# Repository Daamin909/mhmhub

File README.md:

# mhmhub

Made by [Daamin](https://daamin.tech)

Features:

- USB-C input port
- 3x USB-C ports
- 1x USB-A port
- White Case
- Mounted PCB for stability

## Info

this hub is a 3x usbc port + 1x usba hub. it has a usb-c as the power source and connector to the host. it is also very teeny tiny.

I made this hub since i own a macbook and the hub i owned is pretty cheap and ugly. I wanted this hub to match my white keyboard and macropad. i added usb-a for my harddrives and usb-c for my keyboard and macropad.

## PCB

The PCB's size is 25.5mm x 48.5mm

| Schematic                 |
| ------------------------- |
|  |

| Front                 |
| --------------------- |
|  |

| Back                 |
| -------------------- |
|  |

| 3D - Front               |
| ------------------------ |
|  |

| 3D - Back               |
| ----------------------- |
|  |

## Case

The case was made in Fusion360.

## 3D Render:

## BOM - Products

| Name                 | Qty | Final Price - INR (USD) | Link                                                                                                                                       |
| -------------------- | --- | ----------------------- | ------------------------------------------------------------------------------------------------------------------------------------------ |
| PCBA                 | 2   | 2,597.77 ($30.4)        | [here](https://hc-cdn.hel1.your-objectstorage.com/s/v3/5fce6532436acc2e02ca682e6a3f78e5be402c24_screenshot_2025-06-27_at_7.26.42___pm.png) |
| PCB                  | 5   | 1210.01 ($14.16)        | [here](https://hc-cdn.hel1.your-objectstorage.com/s/v3/5fce6532436acc2e02ca682e6a3f78e5be402c24_screenshot_2025-06-27_at_7.26.42___pm.png) |
| USB-C to USB-C cable | 1   | 350 ($4.1)              | [here](https://amzn.in/d/gBN8jyo)                                                                                                          |
| M2 x 6mm Screws      | 25  | 224 ($2.62)             | [here](https://amzn.in/d/dhuYR6N)                                                                                                          |
| M2 Nuts | 50  | 250 ($2.93)             | [here](https://amzn.in/d/iHDKn9j)                                                                                                          |
| Top Case             | 1   | NA                      | print legion                                                                                                                               |
| Bottom Case          | 1   | NA                      | print legion                                                                                                                               |

## Total Pricing

The total comes out to be approximately 4632 INR ($54.21). Does not include 3D - Printed case.

## Notes :-

I want all the three 3D-printed parts to be printed in white color.

Some of the above items, were ordered in packs due to unavailability of singular items.
The pricing might slightly vary due to flash sales, and dollar market trends.

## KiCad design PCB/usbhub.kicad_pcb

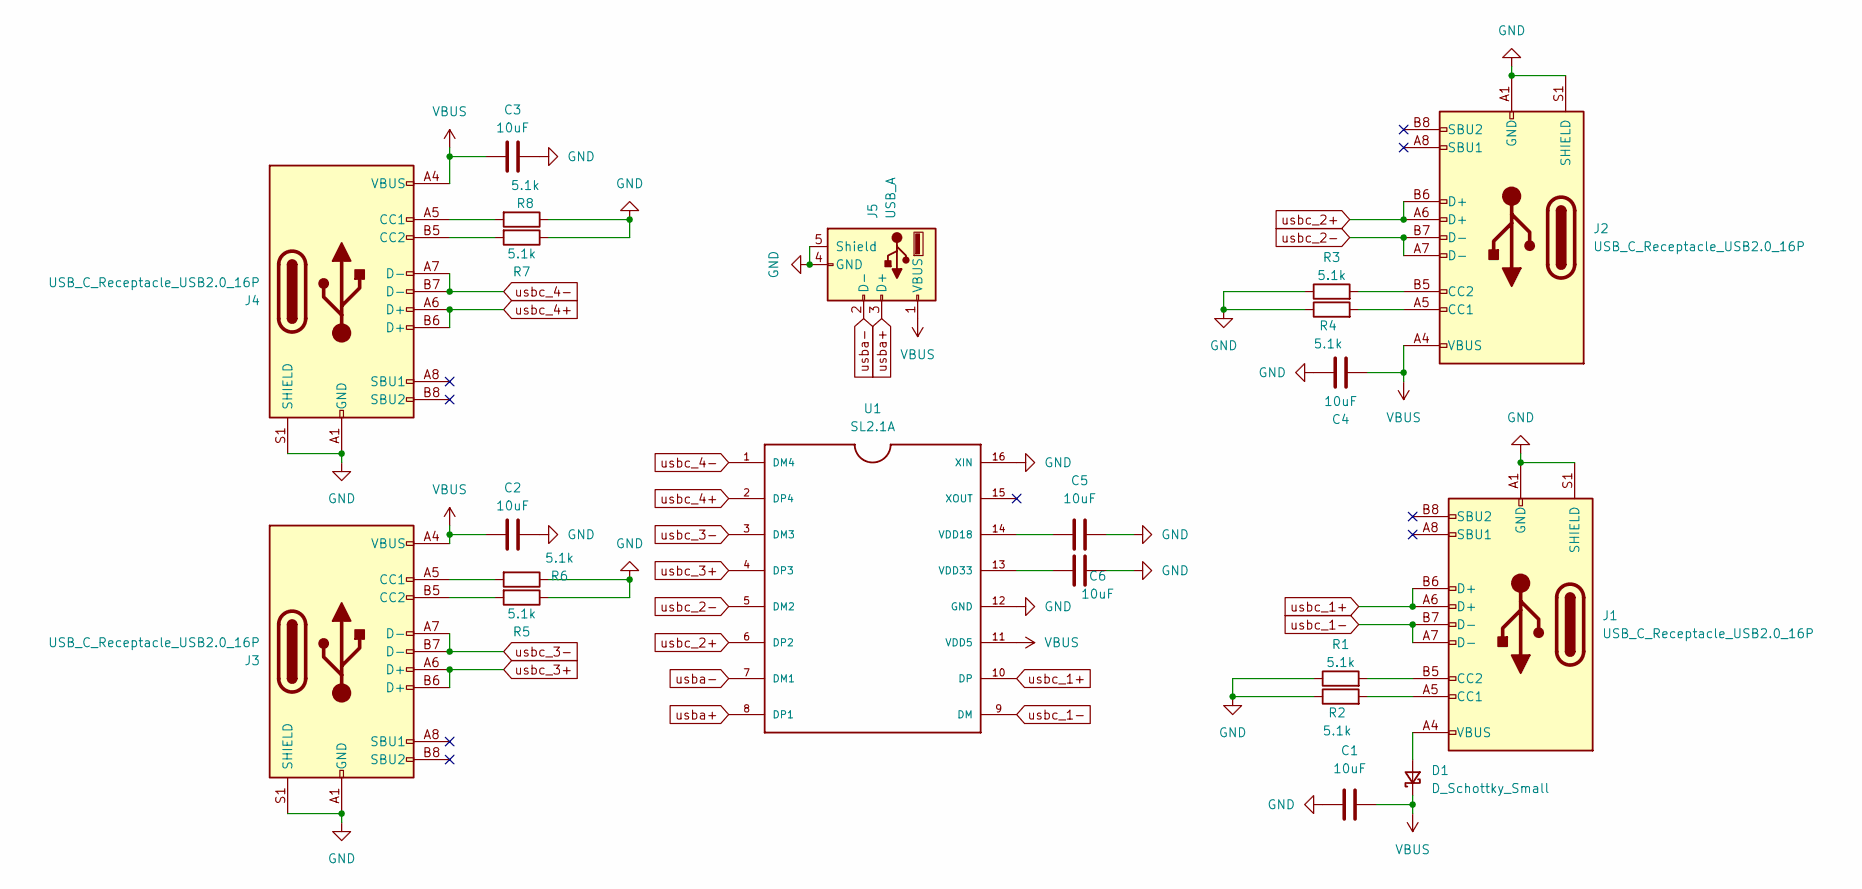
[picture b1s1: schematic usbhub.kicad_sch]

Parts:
C1, C2, C3, C4, C5, C6: 10uF; C_1210_3225Metric
D1: D_Schottky_Small; D_SMA
J1, J2, J3, J4: USB_C_Receptacle_USB2.0_16P; USB_C_Receptacle_G-Switch_GT-USB-7010ASV
J5: USB_A; USB_A_Receptacle_GCT_USB1046
R1, R2, R3, R4, R5, R6, R7, R8: 5.1k; R_0603_1608Metric
U1: SL2.1A; SO16

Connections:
GND: C1.1, C2.1, C3.1, C4.1, C5.2, C6.2, J1.A1 (GND), J1.A12 (GND), J1.B1 (GND), J1.B12 (GND), J1.S1 (SHIELD), J2.A1 (GND), J2.A12 (GND), J2.B1 (GND), J2.B12 (GND), J2.S1 (SHIELD), J3.A1 (GND), J3.A12 (GND), J3.B1 (GND), J3.B12 (GND), J3.S1 (SHIELD), J4.A1 (GND), J4.A12 (GND), J4.B1 (GND), J4.B12 (GND), J4.S1 (SHIELD), J5.4 (GND), J5.5 (Shield), R1.1, R2.1, R3.1, R4.1, R5.1, R6.1, R7.1, R8.1, U1.12 (GND), U1.16 (XIN)
unnamed: D1.2 (A), J1.A4 (VBUS), J1.A9 (VBUS), J1.B4 (VBUS), J1.B9 (VBUS)
unnamed: J1.A5 (CC1), R2.2
unnamed: J1.B5 (CC2), R1.2
unnamed: J2.A5 (CC1), R4.2
unnamed: J2.B5 (CC2), R3.2
unnamed: J3.A5 (CC1), R6.2
unnamed: J3.B5 (CC2), R5.2
unnamed: J4.A5 (CC1), R8.2
unnamed: J4.B5 (CC2), R7.2
unnamed: C5.1, U1.14 (VDD18)
unnamed: C6.1, U1.13 (VDD33)
VBUS: C1.2, C2.2, C3.2, C4.2, D1.1 (K), J2.A4 (VBUS), J2.A9 (VBUS), J2.B4 (VBUS), J2.B9 (VBUS), J3.A4 (VBUS), J3.A9 (VBUS), J3.B4 (VBUS), J3.B9 (VBUS), J4.A4 (VBUS), J4.A9 (VBUS), J4.B4 (VBUS), J4.B9 (VBUS), J5.1 (VBUS), U1.11 (VDD5)
usba+: J5.3 (D+), U1.8 (DP1)
usba-: J5.2 (D-), U1.7 (DM1)
usbc_1+: J1.A6 (D+), J1.B6 (D+), U1.10 (DP)
usbc_1-: J1.A7 (D-), J1.B7 (D-), U1.9 (DM)
usbc_2+: J2.A6 (D+), J2.B6 (D+), U1.6 (DP2)
usbc_2-: J2.A7 (D-), J2.B7 (D-), U1.5 (DM2)
usbc_3+: J3.A6 (D+), J3.B6 (D+), U1.4 (DP3)
usbc_3-: J3.A7 (D-), J3.B7 (D-), U1.3 (DM3)
usbc_4+: J4.A6 (D+), J4.B6 (D+), U1.2 (DP4)
usbc_4-: J4.A7 (D-), J4.B7 (D-), U1.1 (DM4)

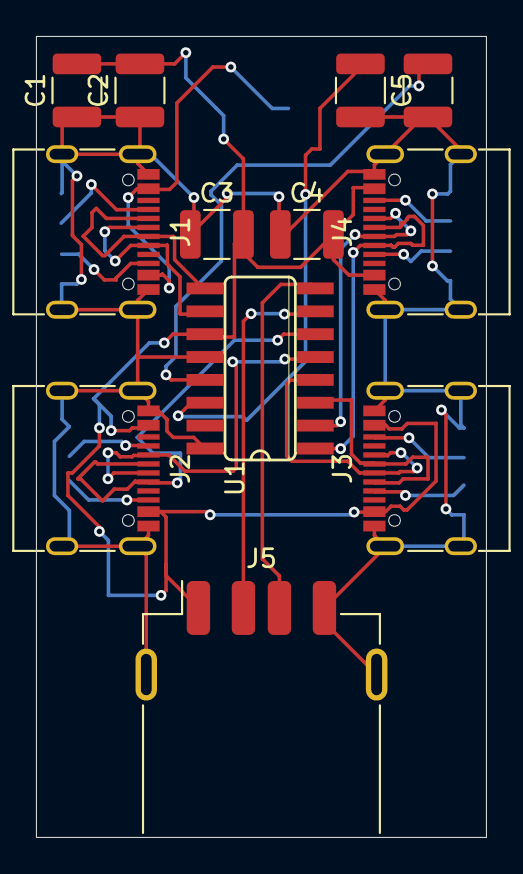
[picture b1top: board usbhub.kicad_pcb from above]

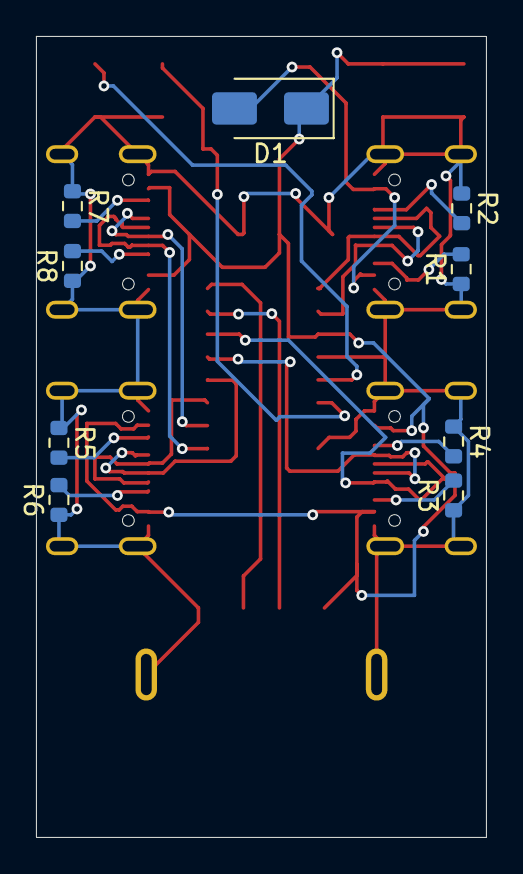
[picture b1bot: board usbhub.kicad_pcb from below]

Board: 2 copper layers, 25.0 x 44.5 mm, 21 parts (9 on the bottom side), 23 nets.

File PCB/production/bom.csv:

Designator,Footprint,Quantity,Value,LCSC Part #
"C1, C2, C3, C4, C5, C6",0805,6,10uF,
D1,D_SMA,1,D_Schottky_Small,
"J1, J2, J3, J4",USB_C_Receptacle_G-Switch_GT-USB-7010ASV,4,USB_C_Receptacle_USB2.0_16P,
J5,USB_A_Receptacle_GCT_USB1046,1,USB_A,
"R1, R2, R3, R4, R5, R6, R7, R8",0603,8,5.1k,
U1,SO16,1,SL2.1A,

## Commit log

2025-06-19 add journal
2025-06-21 add completed pcb
2025-06-21 journaled 2 days
2025-06-27 added assets
2025-06-27 added bom
2025-06-27 journaled: day 3 and 4
2025-06-27 updated pcb
2025-06-27 exported cad
2025-06-27 minor change
2025-06-27 added fasteners to bom
